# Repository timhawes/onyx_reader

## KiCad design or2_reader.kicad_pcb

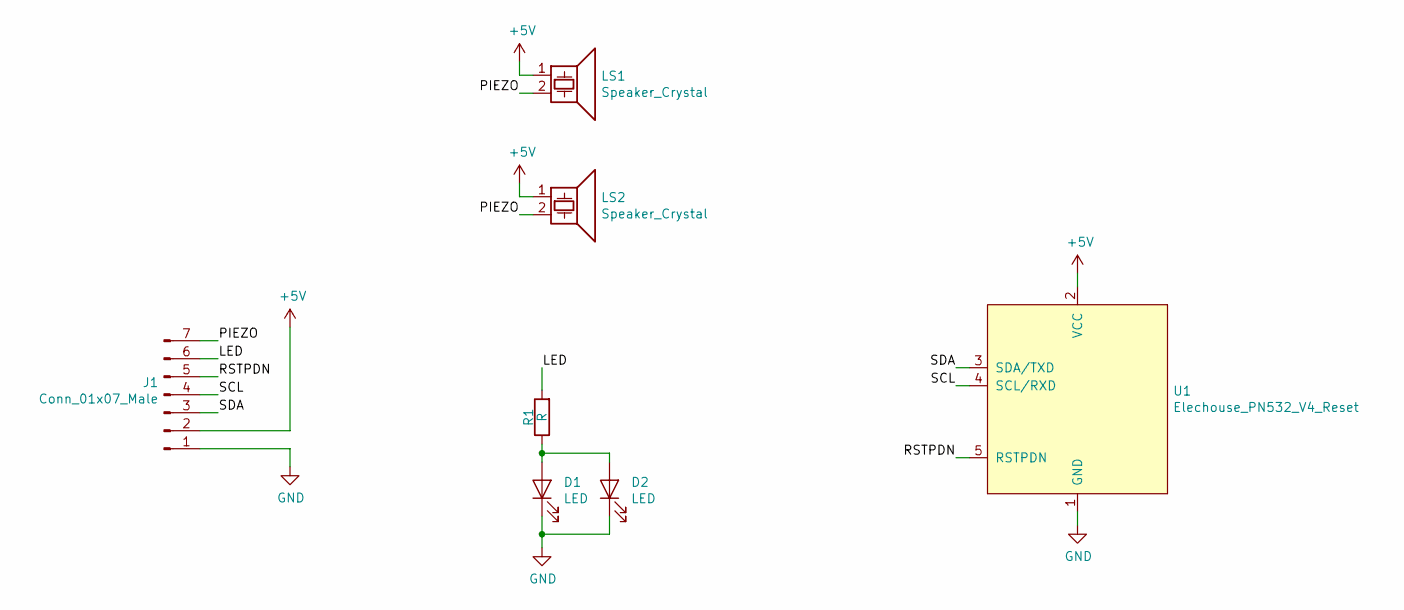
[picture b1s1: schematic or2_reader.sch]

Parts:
D1: LED; LED_D5.0mm
D2: LED; LED_PLCC-2
J1: Conn_01x07_Male; Solder_Connection_7way
LS1: Speaker_Crystal; Buzzer_12x9.5RM7.6
LS2: Speaker_Crystal; Buzzer_Murata_PKMCS0909E4000-R1
R1: R; R_0603_1608Metric
U1: Elechouse_PN532_V4_Reset; ELECHOUSE_PN532_V4_USART_I2C_RESET

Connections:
+5V: J1.2, LS1.1, LS2.1, U1.2 (VCC)
/LED: J1.6, R1.2
/PIEZO: J1.7, LS1.2, LS2.2
/RSTPDN: J1.5, U1.5 (RSTPDN)
/SCL: J1.4, U1.4 (SCL/RXD)
/SDA: J1.3, U1.3 (SDA/TXD)
GND: D1.1 (K), D2.1 (K), J1.1, U1.1 (GND)
unnamed: D1.2 (A), D2.2 (A), R1.1

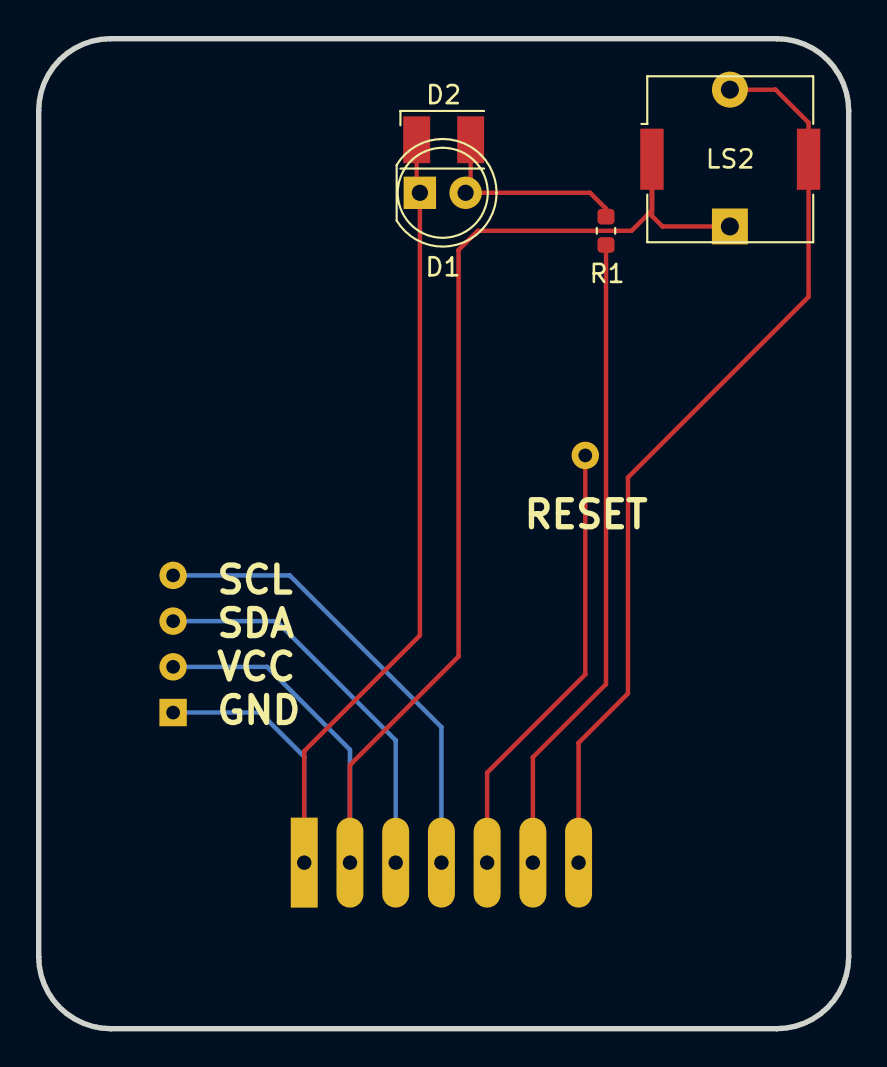
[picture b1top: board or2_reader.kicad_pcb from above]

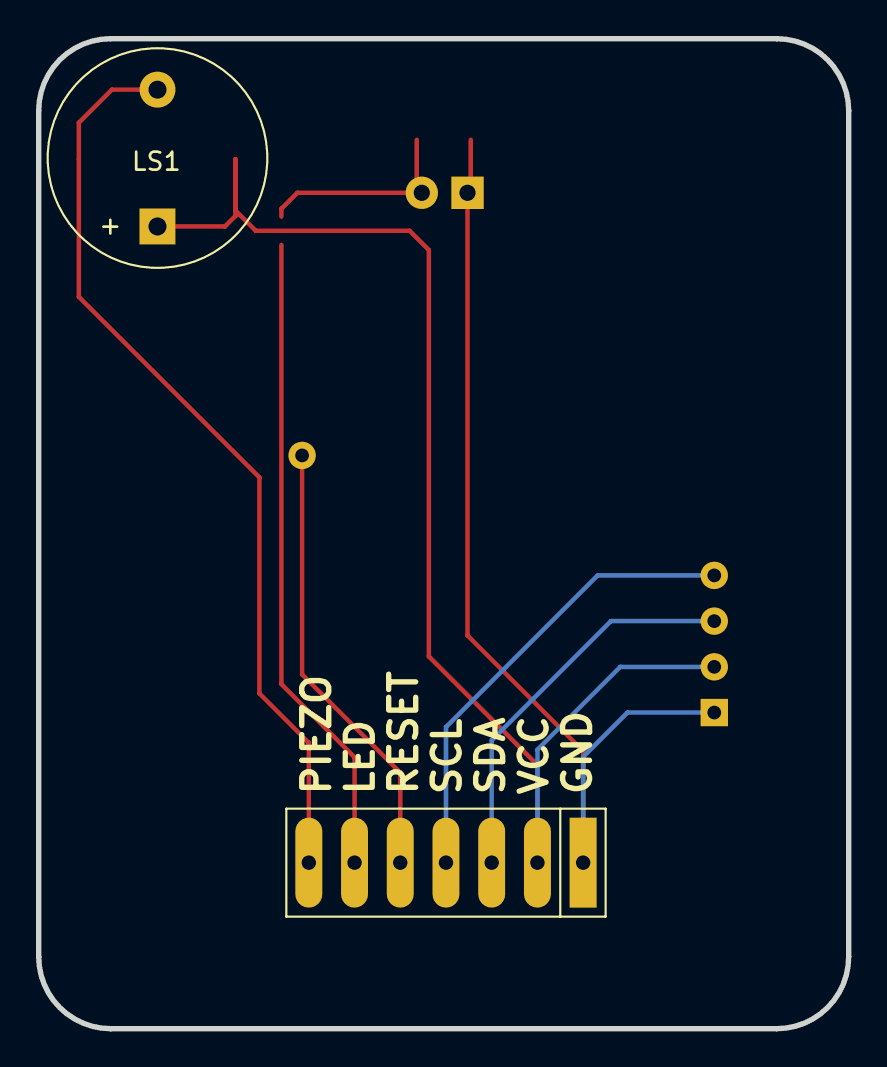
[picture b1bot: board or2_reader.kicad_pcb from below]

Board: 2 copper layers, 45.0 x 55.0 mm, 8 parts (3 on the bottom side), 8 nets.

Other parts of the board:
OUTLINE_55_45_R4: Outline_55_45_R4

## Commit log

2020-08-25 Increase size of RESET pad
